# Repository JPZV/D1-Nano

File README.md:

# D1 Nano

This is a simple project of designs for a D1 Nano, a [D1 Mini](https://www.wemos.cc/en/latest/d1/d1_mini.html) replacement with a smaller size and compatible with ESP32 too!
While I don't have a shop myself, I give the necessary files for making your own free of charge, so feel free to printing your own PCB with your manufacture of choice.

## Advantages

 - Smaller size compared to the D1 Mini
 - All GPIO available with its respective labels
 - Just a few of components to be used
 - Can be powered by 3.3V using 3.3V Test point, or up to 12V by using the 5V Test point (5V is recommended thought)
 - Bigger GPIOs pads compared to the raw MCU
 - Easy to assemble

## Disadvantages

 - Not compatible with breadboards, all GPIOs in use must be soldered in your project
 - [External serial programmer](https://aliexpress.com/item/32842026979.html) must be used
 - No USB connectivity, nor powering by USB

## Assembling

Note: Every component, including the ESP32, can be hand soldered. The GND pad at the back of the ESP32 is not necessary to be soldered.

 0. Download the *.Garber.zip* file for your board in [Releases](https://github.com/JPZV/D1-Nano/releases/latest) and send it to your PCB manufacturer (like PCBWay)
 1. Any resistor marked by R* (R1, R2, R3, etc.) has to be filled with a **1206 10K SMD resistor**.
 2. Any capacitor marked by C* (C1, C2, C3, etc.) has to be filled with a **1206 100nF SMD capacitor** (also named as **1206 0.1uF SMD capacitor**)
 3. Both push buttons are **3x6x2.5mm SMD SPST**.
 4. The regulator (generally marked as **U2**) is an **AMS1117-3.3**.
 5. You can use any type of headers connector for the serial connection, even in any direction that you want. You can even use four Male Jumpers wires when you want to flash without soldering them and then removing them when you finish.
 6. And, for the main MCU, just use the ESP that you want, just be sure to download, buy and assemble the right board (e.g. Use the ESP32 Garber file if you want an ESP32 dev Board). Keep in mind that ESP8266 is also named as ESP12. This board was tested with an ESP12-F and a ESP32-D. The ESP32 Wrover may work but I cannot guarantee it

## Flashing

Note: An [External serial programmer](https://aliexpress.com/item/32842026979.html) is needed

 1. Connect the Serial Programmer to the serial header using Jump Wires.
    - Programmer 5V -> Board 5V
    - Programmer TX -> Board RX
    - Programmer RX -> Board TX
    - Programmer GND -> Board GND
 2. Connect the programmer to your computer
 3. Press and hold the **Reset** button.
 4. Then, press and hold the **Boot** button.
 5. Next, release the **Reset** button while holding the **Boot** button.
 6. Finally, release the **Boot** button. In some ESP32 you have to maintain the **Boot** button pressed while flashing. If you cannot flash your program, then try everything again from step 1 but don't release the **Boot** button until everything is correctly flashed.
 7. Start the Flash process in your program (VS Code, Arduino, ESPHome, Online flasher, etc.) and wait until it finishes.
 8. After it finishes correctly, do a single press in the **Reset** button.

## Contributing

Pull requests are welcome. For major changes, please open an issue first to discuss what you would like to change.

## License

This project uses [MIT license](/LICENSE). This means that you can do whatever you want with this project. You can even make your own board and sell it without needing to give me a commission. But, if you want, you always can [buy me a Coffe](https://ko-fi.com/jpzv5) :)

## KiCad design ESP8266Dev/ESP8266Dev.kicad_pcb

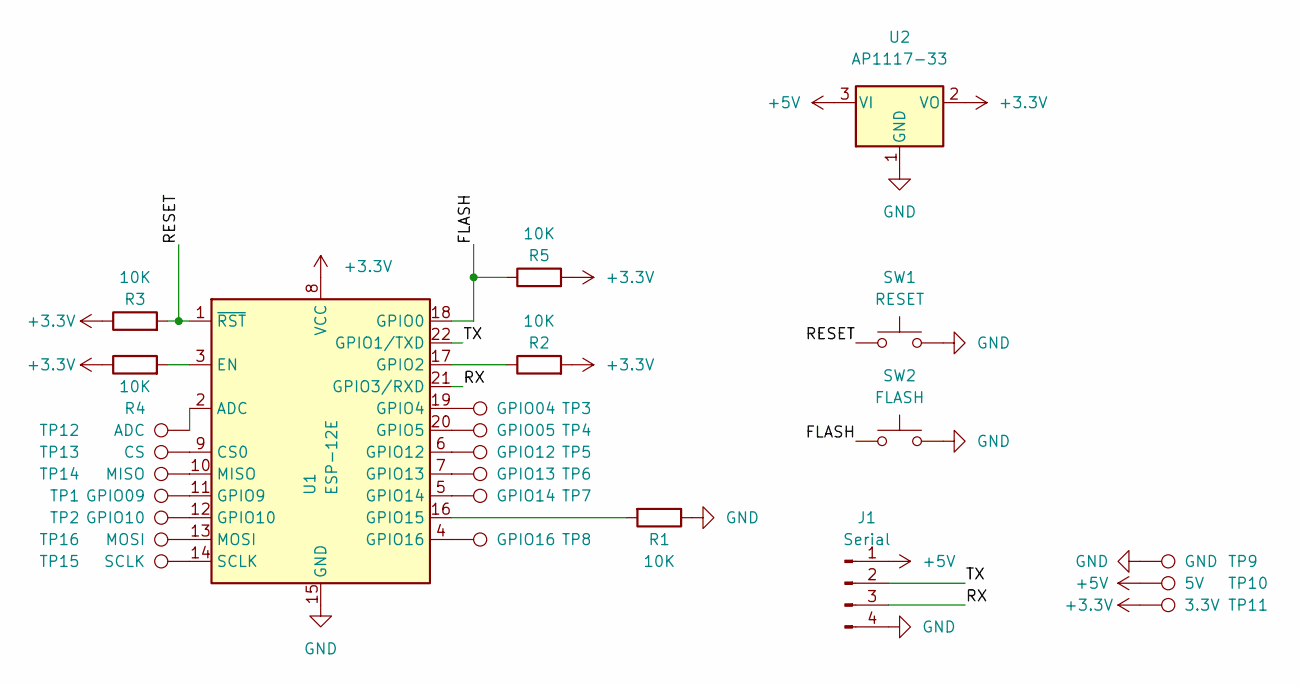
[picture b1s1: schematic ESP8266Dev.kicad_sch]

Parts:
J1: Serial; PinHeader_1x04_P2.54mm_Vertical
R1, R2, R3, R4, R5: 10K; R_1206_3216Metric_Pad1.30x1.75mm_HandSolder
SW1: RESET; SW_SPST_FSMSM
SW2: FLASH; SW_SPST_FSMSM
TP1: GPIO09; TestPoint_Pad_D2.0mm
TP2: GPIO10; TestPoint_Pad_D2.0mm
TP3: GPIO04; TestPoint_Pad_D2.0mm
TP4: GPIO05; TestPoint_Pad_D2.0mm
TP5: GPIO12; TestPoint_Pad_D2.0mm
TP6: GPIO13; TestPoint_Pad_D2.0mm
TP7: GPIO14; TestPoint_Pad_D2.0mm
TP8: GPIO16; TestPoint_Pad_D2.0mm
TP9: GND; TestPoint_Pad_D2.0mm
TP10: 5V; TestPoint_Pad_D2.0mm
TP11: 3.3V; TestPoint_Pad_D2.0mm
TP12: ADC; TestPoint_Pad_D2.0mm
TP13: CS; TestPoint_Pad_D2.0mm
TP14: MISO; TestPoint_Pad_D2.0mm
TP15: SCLK; TestPoint_Pad_D2.0mm
TP16: MOSI; TestPoint_Pad_D2.0mm
U1: ESP-12E
U2: AP1117-33; SOT-223-3_TabPin2

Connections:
+3.3V: R2.2, R3.1, R4.1, R5.2, TP11.1, U1.8 (VCC), U2.2 (VO)
+5V: J1.1, TP10.1, U2.3 (VI)
/FLASH: R5.1, SW2.1, U1.18 (GPIO0)
/RESET: R3.2, SW1.1, U1.1 (~RST)
/RX: J1.3, U1.21 (GPIO3/RXD)
/TX: J1.2, U1.22 (GPIO1/TXD)
GND: J1.4, R1.1, SW1.2, SW2.2, TP9.1, U1.15 (GND), U2.1 (GND)
unnamed: TP12.1, U1.2 (ADC)
unnamed: TP13.1, U1.9 (CS0)
unnamed: R4.2, U1.3 (EN)
unnamed: R2.1, U1.17 (GPIO2)
unnamed: TP3.1, U1.19 (GPIO4)
unnamed: TP4.1, U1.20 (GPIO5)
unnamed: TP1.1, U1.11 (GPIO9)
unnamed: TP2.1, U1.12 (GPIO10)
unnamed: TP5.1, U1.6 (GPIO12)
unnamed: TP6.1, U1.7 (GPIO13)
unnamed: TP7.1, U1.5 (GPIO14)
unnamed: R1.2, U1.16 (GPIO15)
unnamed: TP8.1, U1.4 (GPIO16)
unnamed: TP14.1, U1.10 (MISO)
unnamed: TP16.1, U1.13 (MOSI)
unnamed: TP15.1, U1.14 (SCLK)

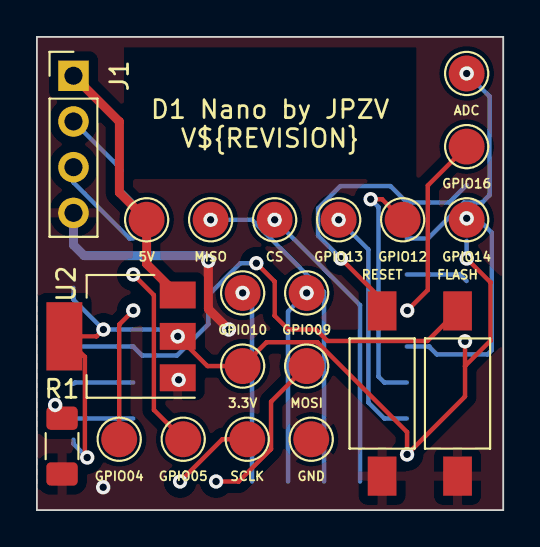
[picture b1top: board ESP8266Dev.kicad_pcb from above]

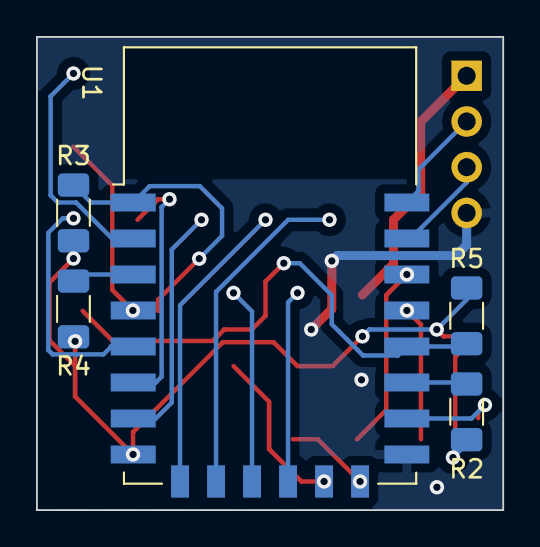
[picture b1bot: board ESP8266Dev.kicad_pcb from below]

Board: 2 copper layers, 25.9 x 26.3 mm, 26 parts (5 on the bottom side), 23 nets.

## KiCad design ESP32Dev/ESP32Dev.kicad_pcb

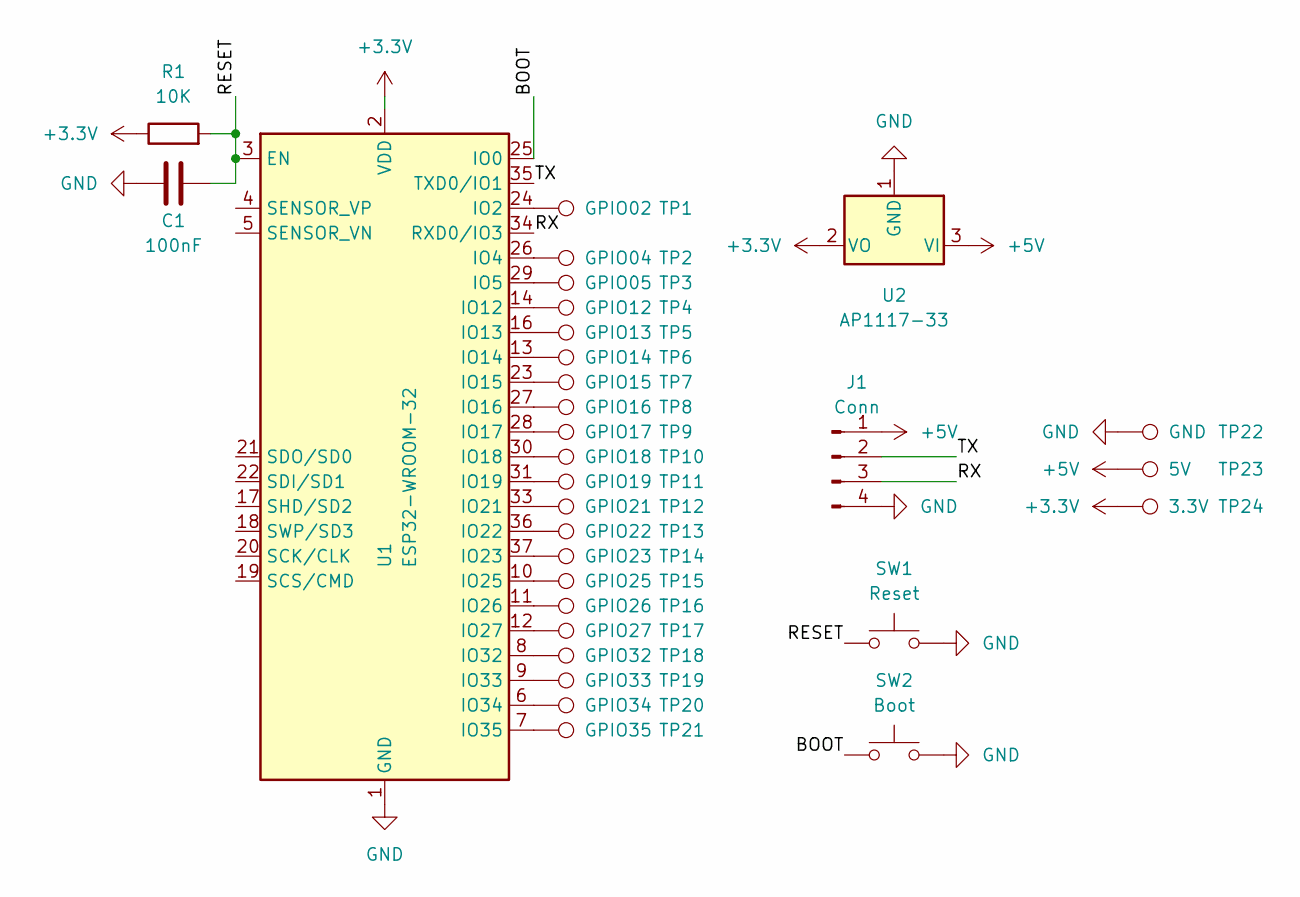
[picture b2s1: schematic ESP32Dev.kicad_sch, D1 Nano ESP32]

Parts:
C1: 100nF; C_1206_3216Metric_Pad1.33x1.80mm_HandSolder
J1: Conn; PinHeader_1x04_P2.54mm_Vertical
R1: 10K; R_1206_3216Metric_Pad1.30x1.75mm_HandSolder
SW1: Reset; SW_SPST_FSMSM
SW2: Boot; SW_SPST_FSMSM
TP1: GPIO02; TestPoint_Pad_D2.0mm
TP2: GPIO04; TestPoint_Pad_D2.0mm
TP3: GPIO05; TestPoint_Pad_D2.0mm
TP4: GPIO12; TestPoint_Pad_D2.0mm
TP5: GPIO13; TestPoint_Pad_D2.0mm
TP6: GPIO14; TestPoint_Pad_D2.0mm
TP7: GPIO15; TestPoint_Pad_D2.0mm
TP8: GPIO16; TestPoint_Pad_D2.0mm
TP9: GPIO17; TestPoint_Pad_D2.0mm
TP10: GPIO18; TestPoint_Pad_D2.0mm
TP11: GPIO19; TestPoint_Pad_D2.0mm
TP12: GPIO21; TestPoint_Pad_D2.0mm
TP13: GPIO22; TestPoint_Pad_D2.0mm
TP14: GPIO23; TestPoint_Pad_D2.0mm
TP15: GPIO25; TestPoint_Pad_D2.0mm
TP16: GPIO26; TestPoint_Pad_D2.0mm
TP17: GPIO27; TestPoint_Pad_D2.0mm
TP18: GPIO32; TestPoint_Pad_D2.0mm
TP19: GPIO33; TestPoint_Pad_D2.0mm
TP20: GPIO34; TestPoint_Pad_D2.0mm
TP21: GPIO35; TestPoint_Pad_D2.0mm
TP22: GND; TestPoint_Pad_D2.0mm
TP23: 5V; TestPoint_Pad_D2.0mm
TP24: 3.3V; TestPoint_Pad_D2.0mm
U1: ESP32-WROOM-32
U2: AP1117-33; SOT-223-3_TabPin2

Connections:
+3.3V: R1.1, TP24.1, U1.2 (VDD), U2.2 (VO)
+5V: J1.1, TP23.1, U2.3 (VI)
/BOOT: SW2.1, U1.25 (IO0)
/RESET: C1.2, R1.2, SW1.1, U1.3 (EN)
/RX: J1.3, U1.34 (RXD0/IO3)
/TX: J1.2, U1.35 (TXD0/IO1)
GND: C1.1, J1.4, SW1.2, SW2.2, TP22.1, U1.1 (GND), U1.15 (GND), U1.38 (GND), U1.39 (GND), U2.1 (GND)
unnamed: TP1.1, U1.24 (IO2)
unnamed: TP2.1, U1.26 (IO4)
unnamed: TP3.1, U1.29 (IO5)
unnamed: TP4.1, U1.14 (IO12)
unnamed: TP5.1, U1.16 (IO13)
unnamed: TP6.1, U1.13 (IO14)
unnamed: TP7.1, U1.23 (IO15)
unnamed: TP8.1, U1.27 (IO16)
unnamed: TP9.1, U1.28 (IO17)
unnamed: TP10.1, U1.30 (IO18)
unnamed: TP11.1, U1.31 (IO19)
unnamed: TP12.1, U1.33 (IO21)
unnamed: TP13.1, U1.36 (IO22)
unnamed: TP14.1, U1.37 (IO23)
unnamed: TP15.1, U1.10 (IO25)
unnamed: TP16.1, U1.11 (IO26)
unnamed: TP17.1, U1.12 (IO27)
unnamed: TP18.1, U1.8 (IO32)
unnamed: TP19.1, U1.9 (IO33)
unnamed: TP20.1, U1.6 (IO34)
unnamed: TP21.1, U1.7 (IO35)

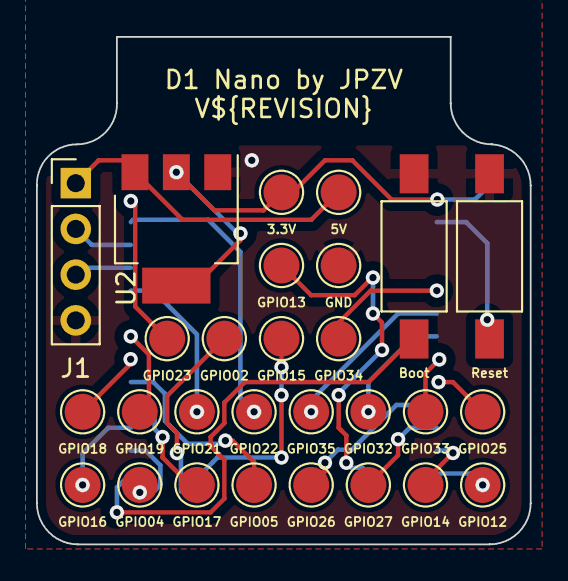
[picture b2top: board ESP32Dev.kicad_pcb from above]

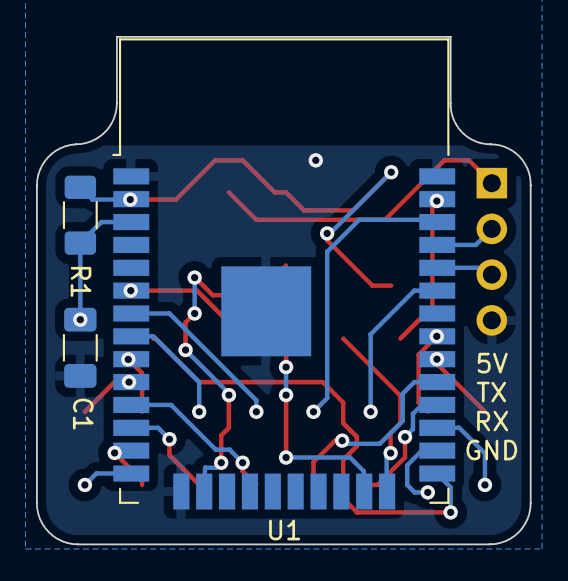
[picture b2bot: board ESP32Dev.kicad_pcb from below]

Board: 2 copper layers, 27.4 x 28.2 mm, 31 parts (3 on the bottom side), 28 nets.

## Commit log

2023-10-11 Added ESP32 Dev Board
2023-10-11 ESP32: Fixed via overlapping GPIO19 text
2023-10-11 ESP32: Fixed capacitor value
2023-10-13 Added ESP8266Dev Board
